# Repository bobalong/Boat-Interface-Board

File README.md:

Boat-Interface-Board
====================

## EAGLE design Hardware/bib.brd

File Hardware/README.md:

Unless specified otherwise, the files contained within are licenced under CC BY-NC 4.0. See LICENSE for the full licence.

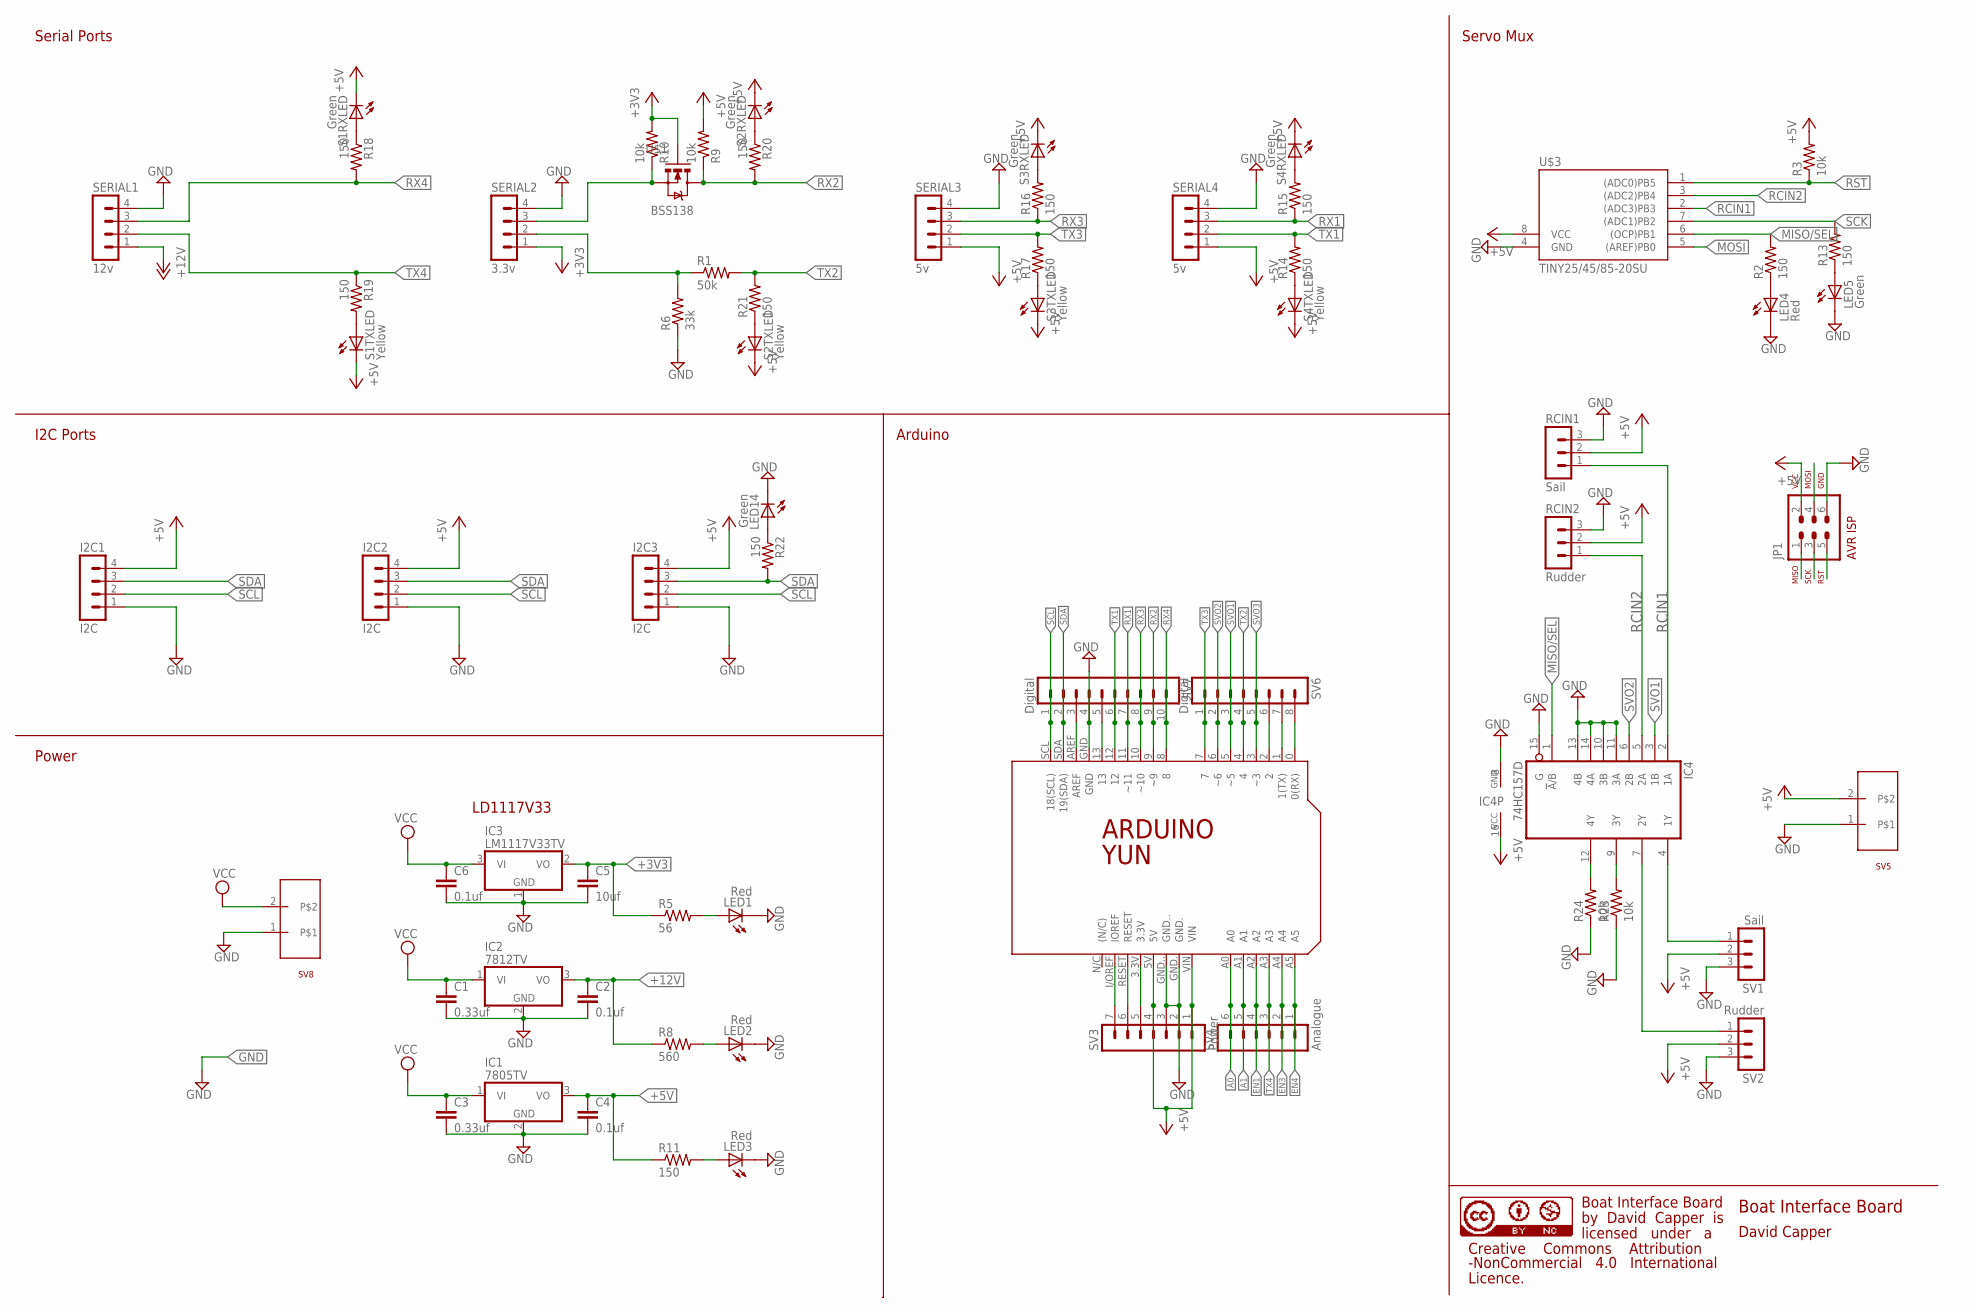
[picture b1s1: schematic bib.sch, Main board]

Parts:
C1, C3: 0.33uf; C0805K; MPN 08053C334KAT2A
C2, C4, C6: 0.1uf; C0805K; MPN 08051C104JAT2A
C5: 10uf; C0805K; MPN CC0805KRX7R8BB333
I2C1, I2C2, I2C3: I2C; MA04-1
IC1: 7805TV; TO220V; MPN L7805ACV
IC2: 7812TV; TO220V; MPN L7812ACV
IC3: LM1117V33TV; TO220V; MPN LD1117V33
IC4: 74HC157D; SO16; MPN SN74HC157D
JP1: AVR-ISP-6VERT; AVR-ISP-6
LED1, LED2, LED3: Red; SML1206; MPN KPT-3216SRC-J4
LED4: Red; SML1206; MPN KPT-3216SGC
LED5, LED14: Green; SML1206; MPN KPT-3216SGC
PCB2: ARDUINO_YUNARDUINO_YUN; ARDUINO_YUN
R1: 50k; M0805; MPN CRCW080533K0FKEA
R2, R11, R13, R14, R15, R16, R17, R18, R19, R20, R21, R22: 150; R0805; MPN CRCW0805150RFKEAHP
R3: 10k; R0805; MPN CRCW0805150RFKEAHP
R5: 56; R0805; MPN CRCW080556R0FKEAHP
R6: 33k; M0805; MPN CRCW080549K9FKEA
R8: 560; R0805; MPN CRCW0805560RFKEAHP
R9, R10: 10k; M0805; MPN CRCW080510K0FKEA
R23, R24: 10k; R0805; MPN CRCW080510K0FKEA
RCIN1: Sail; MA03-1
RCIN2: Rudder; MA03-1
S1RXLED, S2RXLED, S3RXLED, S4RXLED: Green; SML1206; MPN KPT-3216SGC
S1TXLED, S2TXLED, S3TXLED, S4TXLED: Yellow; SML1206; MPN KPT-3216SYCK
SERIAL1: 12v; MA04-1
SERIAL2: 3.3v; MA04-1
SERIAL3, SERIAL4: 5v; MA04-1
SV1: Sail; MA03-1
SV2: Rudder; MA03-1
SV3: Power; MA07-1
SV4: Analogue; MA06-1
SV5, SV8: MA02; MA02-1
SV6: Digital; MA08-1
SV7: Digital; MA10-1
U$1: BSS138; SOT23; MPN BSS138
U$3: TINY25/45/85-20SU; SOIC8; MPN ATTINY25-20SU

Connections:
+3V3: C5.1, IC3.2 (VO), R5.1, R10.2, SERIAL2.1, U$1.1 (G)
+5V: C4.1, I2C1.4, I2C2.4, I2C3.4, IC1.3 (VO), IC4.16 (VCC), JP1.2, PCB2.5V, PCB2.VIN, R3.2, R9.2, R11.1, RCIN1.2, RCIN2.2, S1RXLED.C, S1TXLED.C, S2RXLED.C, S2TXLED.C, S3RXLED.C, S3TXLED.C, S4RXLED.C, S4TXLED.C, SERIAL3.1, SERIAL4.1, SV1.2, SV2.2, SV3.1, SV3.4, SV5.2, U$3.8 (VCC)
+12V: C2.1, IC2.3 (VO), R8.1, SERIAL1.1
A0: PCB2.A0, SV4.6
A1: PCB2.A1, SV4.5
EN1: PCB2.A2, SV4.4
EN3: PCB2.A4, SV4.2
EN4: PCB2.A5, SV4.1
GND: C1.2, C2.2, C3.2, C4.2, C5.2, C6.2, I2C1.1, I2C2.1, I2C3.1, IC1.2 (GND), IC2.2 (GND), IC3.1 (GND), IC4.8 (GND), IC4.10 (3B), IC4.11 (3A), IC4.13 (4B), IC4.14 (4A), IC4.15 (G), JP1.6, LED1.C, LED2.C, LED3.C, LED4.C, LED5.C, LED14.C, PCB2.GND, PCB2.GND., PCB2.GND.., R6.1, R23.1, R24.1, RCIN1.3, RCIN2.3, SERIAL1.4, SERIAL2.4, SERIAL3.4, SERIAL4.4, SV1.3, SV2.3, SV3.2, SV3.3, SV5.1, SV7.4, SV8.1, U$3.4 (GND)
MEH: PCB2.2, SV6.6
MISO/SEL: IC4.1 (!A!/B), JP1.1, R2.2, U$3.6 ((OCP)PB1)
MOSI: JP1.4, U$3.5 ((AREF)PB0)
unnamed: R10.1, SERIAL2.3, U$1.2 (S)
unnamed: LED4.A, R2.1
unnamed: IC4.12 (4Y), R24.2
unnamed: R1.1, R6.2, SERIAL2.2
unnamed: IC4.4 (1Y), SV1.1
unnamed: IC4.7 (2Y), SV2.1
unnamed: PCB2.3.3V, SV3.5
unnamed: PCB2.RESET, SV3.6
unnamed: PCB2.I/OREF (IOREF), SV3.7
unnamed: PCB2.1 (1(TX)), SV6.7
unnamed: PCB2.0 (0(RX)), SV6.8
unnamed: PCB2.AREF, SV7.3
unnamed: PCB2.13, SV7.5
unnamed: IC4.9 (3Y), R23.2
unnamed: LED1.A, R5.2
unnamed: LED2.A, R8.2
unnamed: LED3.A, R11.2
unnamed: R18.1, S1RXLED.A
unnamed: R19.2, S1TXLED.A
unnamed: R20.1, S2RXLED.A
unnamed: R21.1, S2TXLED.A
unnamed: LED14.A, R22.1
unnamed: R15.2, S4RXLED.A
unnamed: R14.1, S4TXLED.A
unnamed: R16.2, S3RXLED.A
unnamed: R17.1, S3TXLED.A
unnamed: LED5.A, R13.1
RCIN1: IC4.2 (1A), RCIN1.1, U$3.2 ((ADC3)PB3)
RCIN2: IC4.5 (2A), RCIN2.1, U$3.3 ((ADC2)PB4)
RST: JP1.5, R3.1, U$3.1 ((ADC0)PB5)
RX1: PCB2.11 (~11), R15.1, SERIAL4.3, SV7.7
RX2: PCB2.9 (~9), R9.1, R20.2, SV7.9, U$1.3 (D)
RX3: PCB2.10 (~10), R16.1, SERIAL3.3, SV7.8
RX4: PCB2.8, R18.2, SERIAL1.3, SV7.10
SCK: JP1.3, R13.2, U$3.7 ((ADC1)PB2)
SCL: I2C1.2, I2C2.2, I2C3.2, PCB2.SCL (18(SCL)), SV7.1
SDA: I2C1.3, I2C2.3, I2C3.3, PCB2.SDA (19(SDA)), R22.2, SV7.2
SVO1: IC4.3 (1B), PCB2.5 (~5), SV6.3
SVO2: IC4.6 (2B), PCB2.6 (~6), SV6.2
SVO3: PCB2.3 (~3), SV6.5
TX1: PCB2.12, R14.2, SERIAL4.2, SV7.6
TX2: PCB2.4, R1.2, R21.2, SV6.4
TX3: PCB2.7, R17.2, SERIAL3.2, SV6.1
TX4: PCB2.A3, R19.1, SERIAL1.2, SV4.3
VCC: C1.1, C3.1, C6.1, IC1.1 (VI), IC2.1 (VI), IC3.3 (VI), SV8.2

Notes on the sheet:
Serial Ports
I2C Ports
Power
Arduino
Servo Mux
LD1117V33
Boat Interface Board
David Capper
by David Capper is
licensed under a
Creative Commons Attribution
-NonCommercial 4.0 International
Licence.

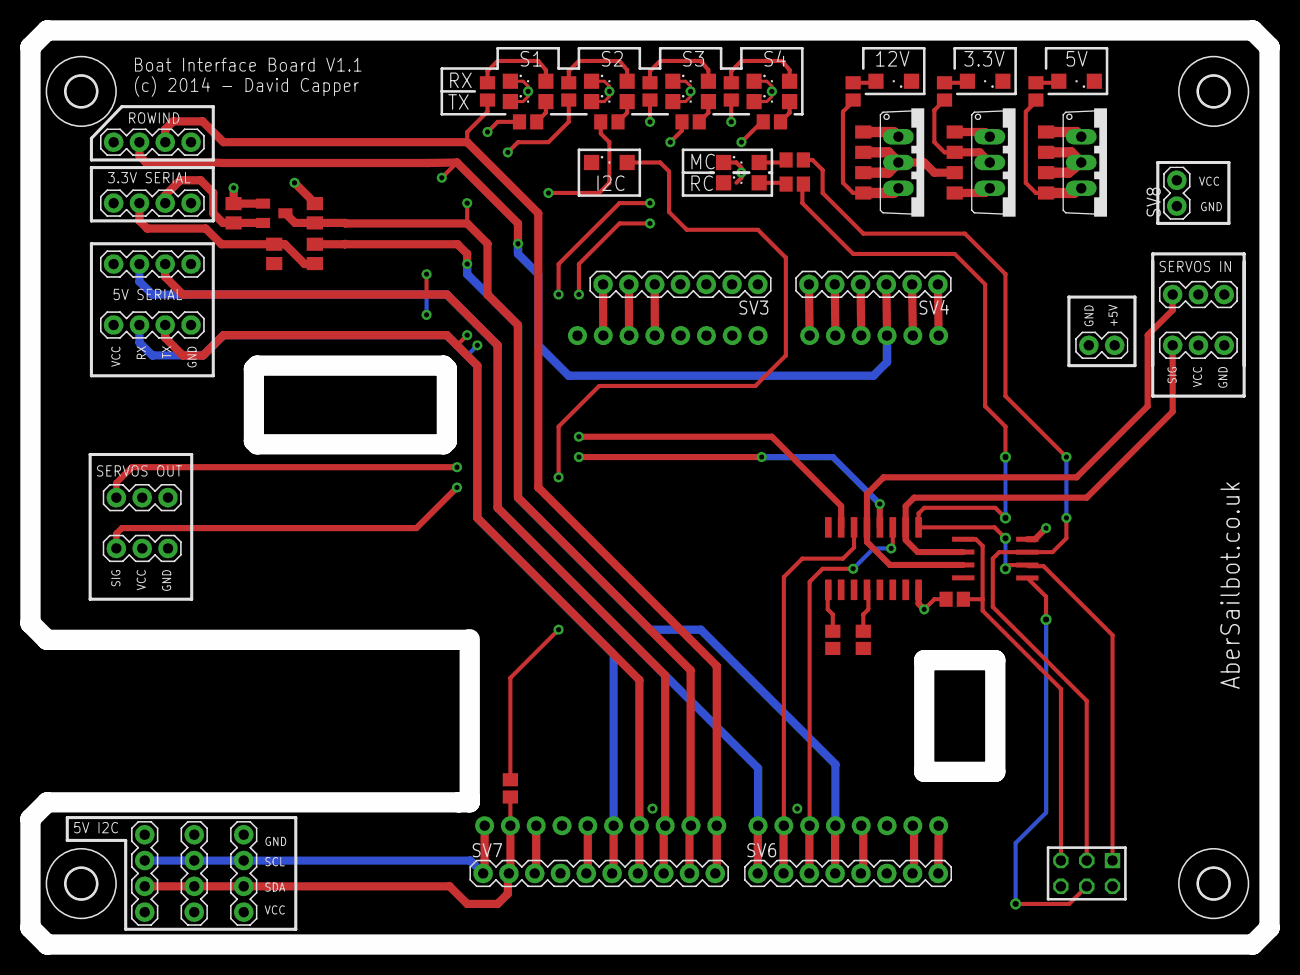
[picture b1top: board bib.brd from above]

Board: 4 copper layers, 122.0 x 90.0 mm, 70 parts (0 on the bottom side), 57 nets.

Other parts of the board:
U$2, U$4, U$5, U$6: 3,0

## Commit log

2014-08-08 Added License
2014-08-08 Added files to hardware
2014-08-08 added read me for firmware
2014-08-08 added readmes
2014-09-01 fixed errors bringing this up to V1.1
2014-09-01 duped pdf removed

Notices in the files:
Hardware/README.md:
Creative Commons Attribution-NonCommercial 4.0 International License
Hardware/bib.brd:
(c) 2014 - David Capper
